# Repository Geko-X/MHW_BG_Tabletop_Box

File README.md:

Hardware lighting and effects "box" for MHW:BG.

Also shows player and card counts on a 7-segment display.

# Hardware
- Raspberry Pi Pico
- MAX7219 7-segment display
- 2x potentiometers
- 2x WS2812B lightstrips (16 LEDs and "many" LEDs)
- 10x tactile buttons
  - 5 for time and card counts
  - 5 for effects

## Pins

- Potentiometers on GP 26 and 27 (Physcial pins 31 and 32)
  - Wire to ADC_VREF (pin 35) and ADC_GND (pin 33)
- Tactile buttons on GP 6-15 (Physical pins 9-12, 14-17, 19, 20)
  - Wire to 3V3 OUT (pin 36)
    
- MAX7219
  - VCC: VBUS
  - DIN: GP 3 (Phsycial pin 5)
  - CLOCK: GP 2 (Phsycial pin 4)
  - CS: GP 5 (Phsycial pin 7)
    
Small WS2812B:
  - VCC: VBUS
  - DIN: GP 17 (Physcial pin 22)
    
Large WS2812B:
  - VCC: VBUS
  - DIN: GP 16 (Phsycial pin 21)

## Wiring

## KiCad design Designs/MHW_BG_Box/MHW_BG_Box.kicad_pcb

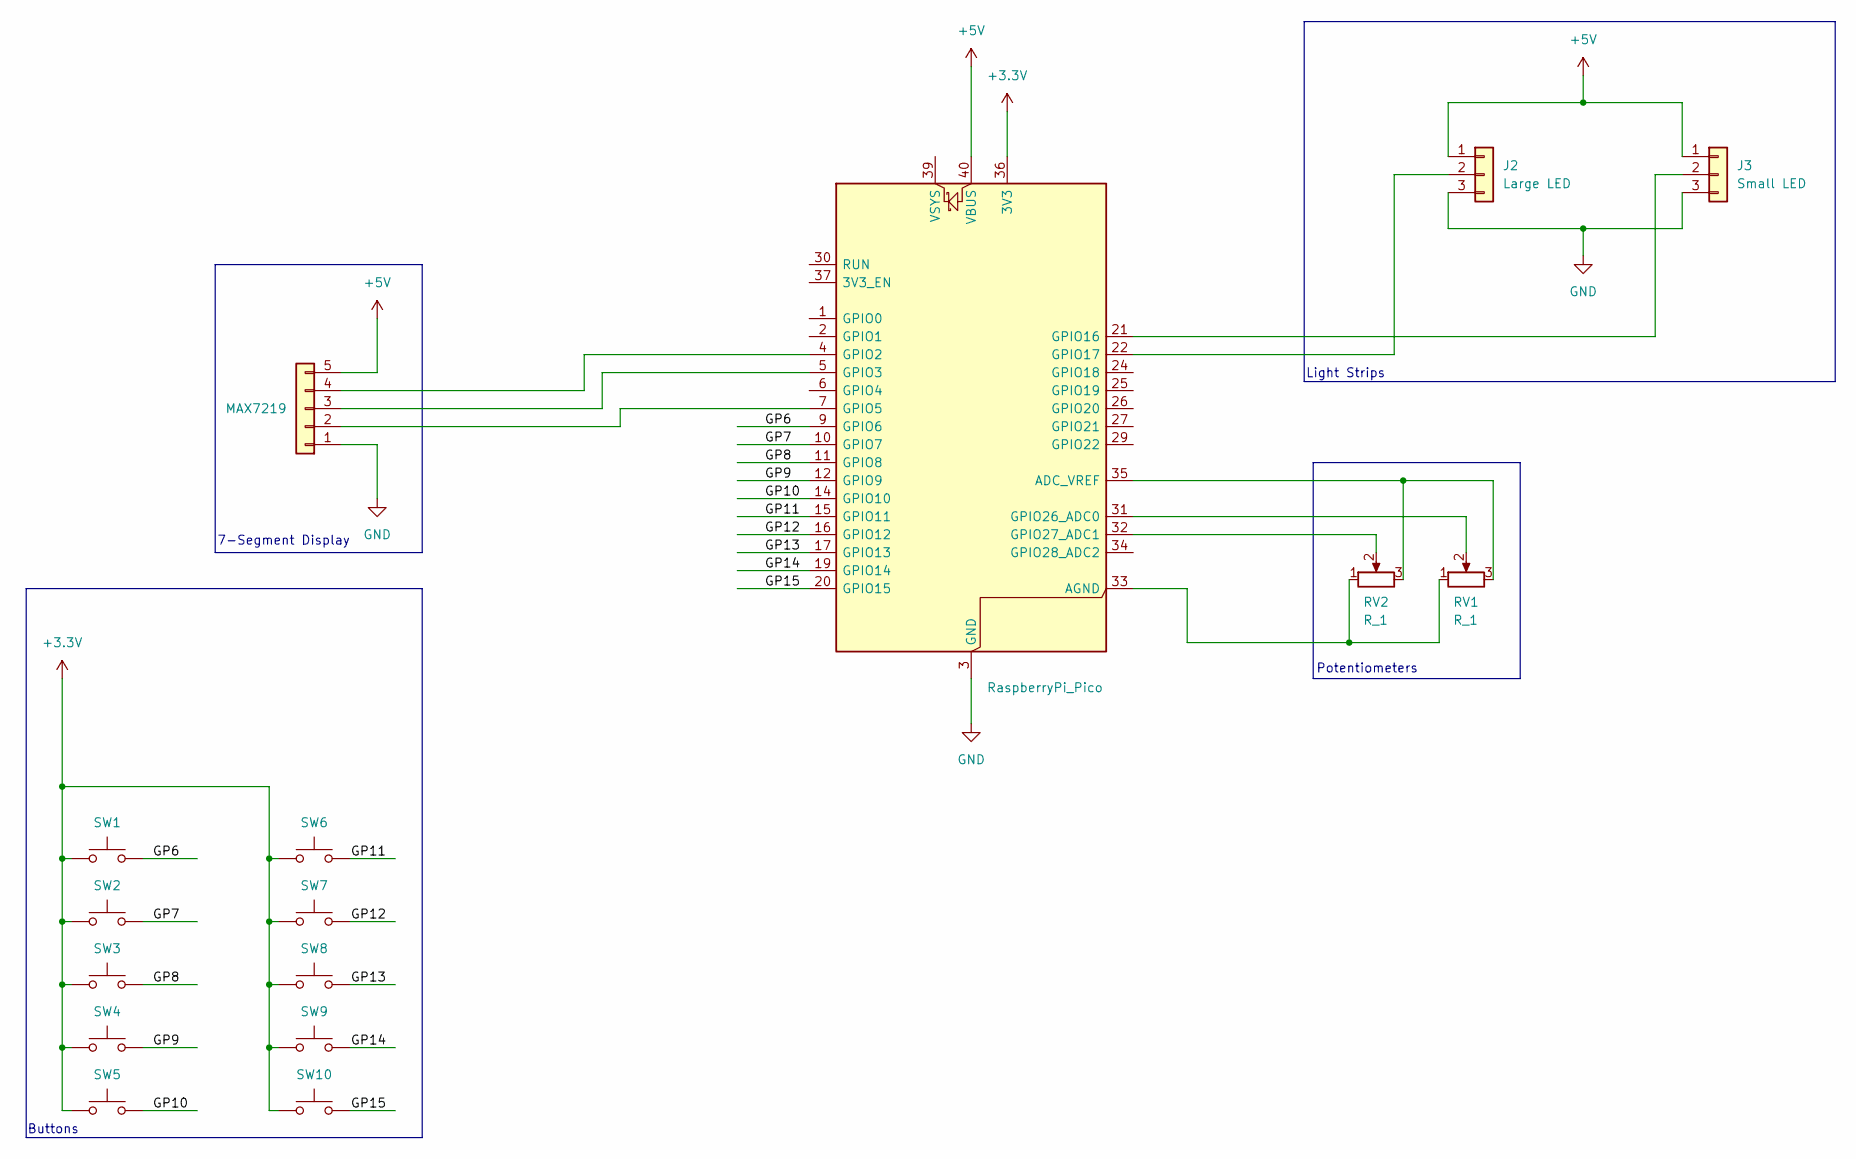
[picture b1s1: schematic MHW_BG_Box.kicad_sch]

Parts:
A1: RaspberryPi_Pico; RaspberryPi_Pico_Common_THT
J1: MAX7219; PinSocket_1x05_P2.54mm_Vertical
J2: Large LED; JST_PH_B3B-PH-K_1x03_P2.00mm_Vertical
J3: Small LED; JST_PH_B3B-PH-K_1x03_P2.00mm_Vertical
RV1, RV2: R_1; PinHeader_1x03_P2.54mm_Vertical
SW1, SW2, SW3, SW4, SW5, SW6, SW7, SW8, SW9, SW10: SW_Push; SW_PUSH-12mm

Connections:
+3.3V: A1.36 (3V3), SW1.1, SW2.1, SW3.1, SW4.1, SW5.1, SW6.1, SW7.1, SW8.1, SW9.1, SW10.1
+5V: A1.40 (VBUS), J1.5, J2.1, J3.1
/GP6: A1.9 (GPIO6), SW1.2
/GP7: A1.10 (GPIO7), SW2.2
/GP8: A1.11 (GPIO8), SW3.2
/GP9: A1.12 (GPIO9), SW4.2
/GP10: A1.14 (GPIO10), SW5.2
/GP11: A1.15 (GPIO11), SW6.2
/GP12: A1.16 (GPIO12), SW7.2
/GP13: A1.17 (GPIO13), SW8.2
/GP14: A1.19 (GPIO14), SW9.2
/GP15: A1.20 (GPIO15), SW10.2
GND: A1.3 (GND), A1.8 (GND), A1.13 (GND), A1.18 (GND), A1.23 (GND), A1.28 (GND), A1.38 (GND), J1.1, J2.3, J3.3
unnamed: A1.35 (ADC_VREF), RV1.3, RV2.3
unnamed: A1.33 (AGND), RV1.1, RV2.1
unnamed: A1.4 (GPIO2), J1.4
unnamed: A1.5 (GPIO3), J1.3
unnamed: A1.7 (GPIO5), J1.2
unnamed: A1.21 (GPIO16), J3.2
unnamed: A1.22 (GPIO17), J2.2
unnamed: A1.31 (GPIO26_ADC0), RV1.2
unnamed: A1.32 (GPIO27_ADC1), RV2.2

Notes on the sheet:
Buttons
Light Strips
7-Segment Display
Potentiometers

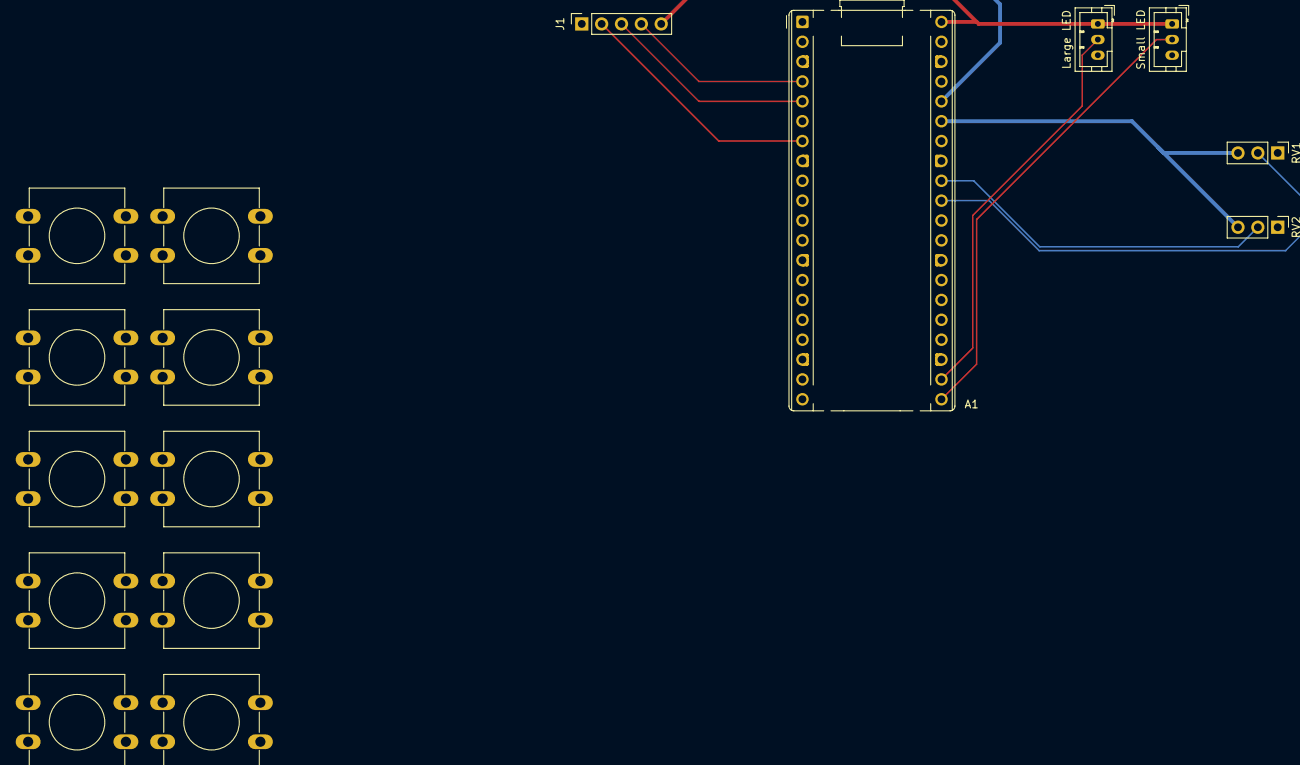
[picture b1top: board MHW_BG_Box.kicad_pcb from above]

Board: 2 copper layers, 16 parts (0 on the bottom side), 22 nets.

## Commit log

2024-03-30 Initial commit + dump
2024-03-30 Add second potentiometer
2024-04-02 Move pin constants to pico_constants.py
2024-04-03 Add glowbit stick
2024-04-04 Button testing
2024-04-05 Control glowbit stick with pots
2024-04-05 Add all buttons
2024-04-06 + Use debounced buttons + Use 2nd pot as start colour changer
2024-04-07 + Test patterns
2024-04-08 + Pre-game setup buttons
2024-04-09 + Use asyncio for async functions. LED libraries still block execution
2024-04-11 + Flash-flash, FLASH pattern
2024-04-14 + Flash now uses time-based logic
2024-04-20 + Update hardware + Update pins + Add wiring diagram + Add extra buttons + Map control buttons to controls and effect buttons to effects
2024-04-22 + Hardware test with all hardware connected + Add additional effects + Fix light strips using same state machine
2024-04-23 + Update wiring diagram
2024-05-09 Updated main
2024-08-01 Replace Tziti Flash effect with Invasion
2024-08-02 Adjust timings on invasion flashes
2024-08-02 Adjust patterns
2025-06-04 Moved electronics design files into /Designs
2025-06-10 Update LED headers
2025-07-19 + Update light effetcs
